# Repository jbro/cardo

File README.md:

# Cardo Keyboard

This is a custom ergonomic wireless keyboard. The design language is based on the [Reviung41](https://github.com/gtips/reviung/tree/master) and the key layout is based on the [Atreus](https://atreus.technomancy.us/) keyboard without thumb keys.

## Features

- Columnar layout
- Low profile
  - Kailh Choc V1 switches
- Sub 40% layout
  - 36 1u keys
  - 1.5u space bar
- Wireless connectivity
- Low part count
  - No diodes
  - Shift register based with a single column
  - Mostly SMD components
- Seeed XIAO nrf52840 micro controller
- 3D printable case (TBD)

## Keymap

## Schematics

## PCB

[3d model](https://github.com/jbro/cardo/blob/main/images/cardo.stl)

## BOM

| Part | Quantity | Description | Link |
| ---- | -------- | ----------- | ---- |
| S2B-PH-SM4-TB(LF)(SN) | 1 | JST PH2 connector | [Mouser](https://www.mouser.dk/ProductDetail/306-S2BPHSM4TBLFSN) |
| SSAJ110100 | 1 | Slide switch | [Mouser](https://www.mouser.dk/ProductDetail/688-SSAJ110100) |
| 7305-0-15-15-47-27-10-0 | 74 | Mill Max 7305 "hot swap" socket | [Mouser](https://www.mouser.dk/ProductDetail/575-7305015154727100) |
| EC05E1220401 | 2 | Rotary encoder | [Mouser](https://www.mouser.dk/ProductDetail/688-EC05E1220401) |
| SN74HCS596DR | 5 | TI shift register with open-drain outputs | [Mouser](https://www.mouser.dk/ProductDetail/Texas-Instruments/SN74HCS596DR) |
| 102010448 | 1 | Seeed XIAO nrf52840 | [Mouser](https://www.mouser.dk/ProductDetail/713-102010448) or  [Seeed studio](https://www.seeedstudio.com/Seeed-XIAO-BLE-nRF52840-p-5201.html) |
| LPR-CHC-SNS-010 | 37 | Kailh Choc Sunset tactile V1 switches | [Splitkb](https://splitkb.com/products/sunset-kailh-low-profile-choc-switches?variant=42742153871619) |
| KSM-MGG-1UN-010 | 34 | 1u MBK PBT Coloured Blank Keycaps | [Splitkb](https://splitkb.com/products/mbk-pbt-coloured-blank-keycaps?variant=49589854011739) |
| KSM-MGG-1UH-002 | 2 | 1u MBK PBT Coloured Blank Keycaps (Homing) | [Splitkb](https://splitkb.com/products/mbk-pbt-coloured-blank-keycaps?variant=49589854404955) |
| KSM-MGG-1U5-002 | 1 | 1.5u MBK PBT Coloured Blank Keycap | [Splitkb](https://splitkb.com/products/mbk-pbt-coloured-blank-keycaps?variant=49589855977819) |
| AM3144y | 1 | Li-Pol battery 60mAh, 3.7V, 501015 | [Ampul](https://ampul.eu/en/battery/4453-li-pol-battery-60mah-37v-501015) |

## License

This project is licensed under the [Unlicense](https://unlicense.org/). Feel free to use, modify, and distribute this project as you wish.

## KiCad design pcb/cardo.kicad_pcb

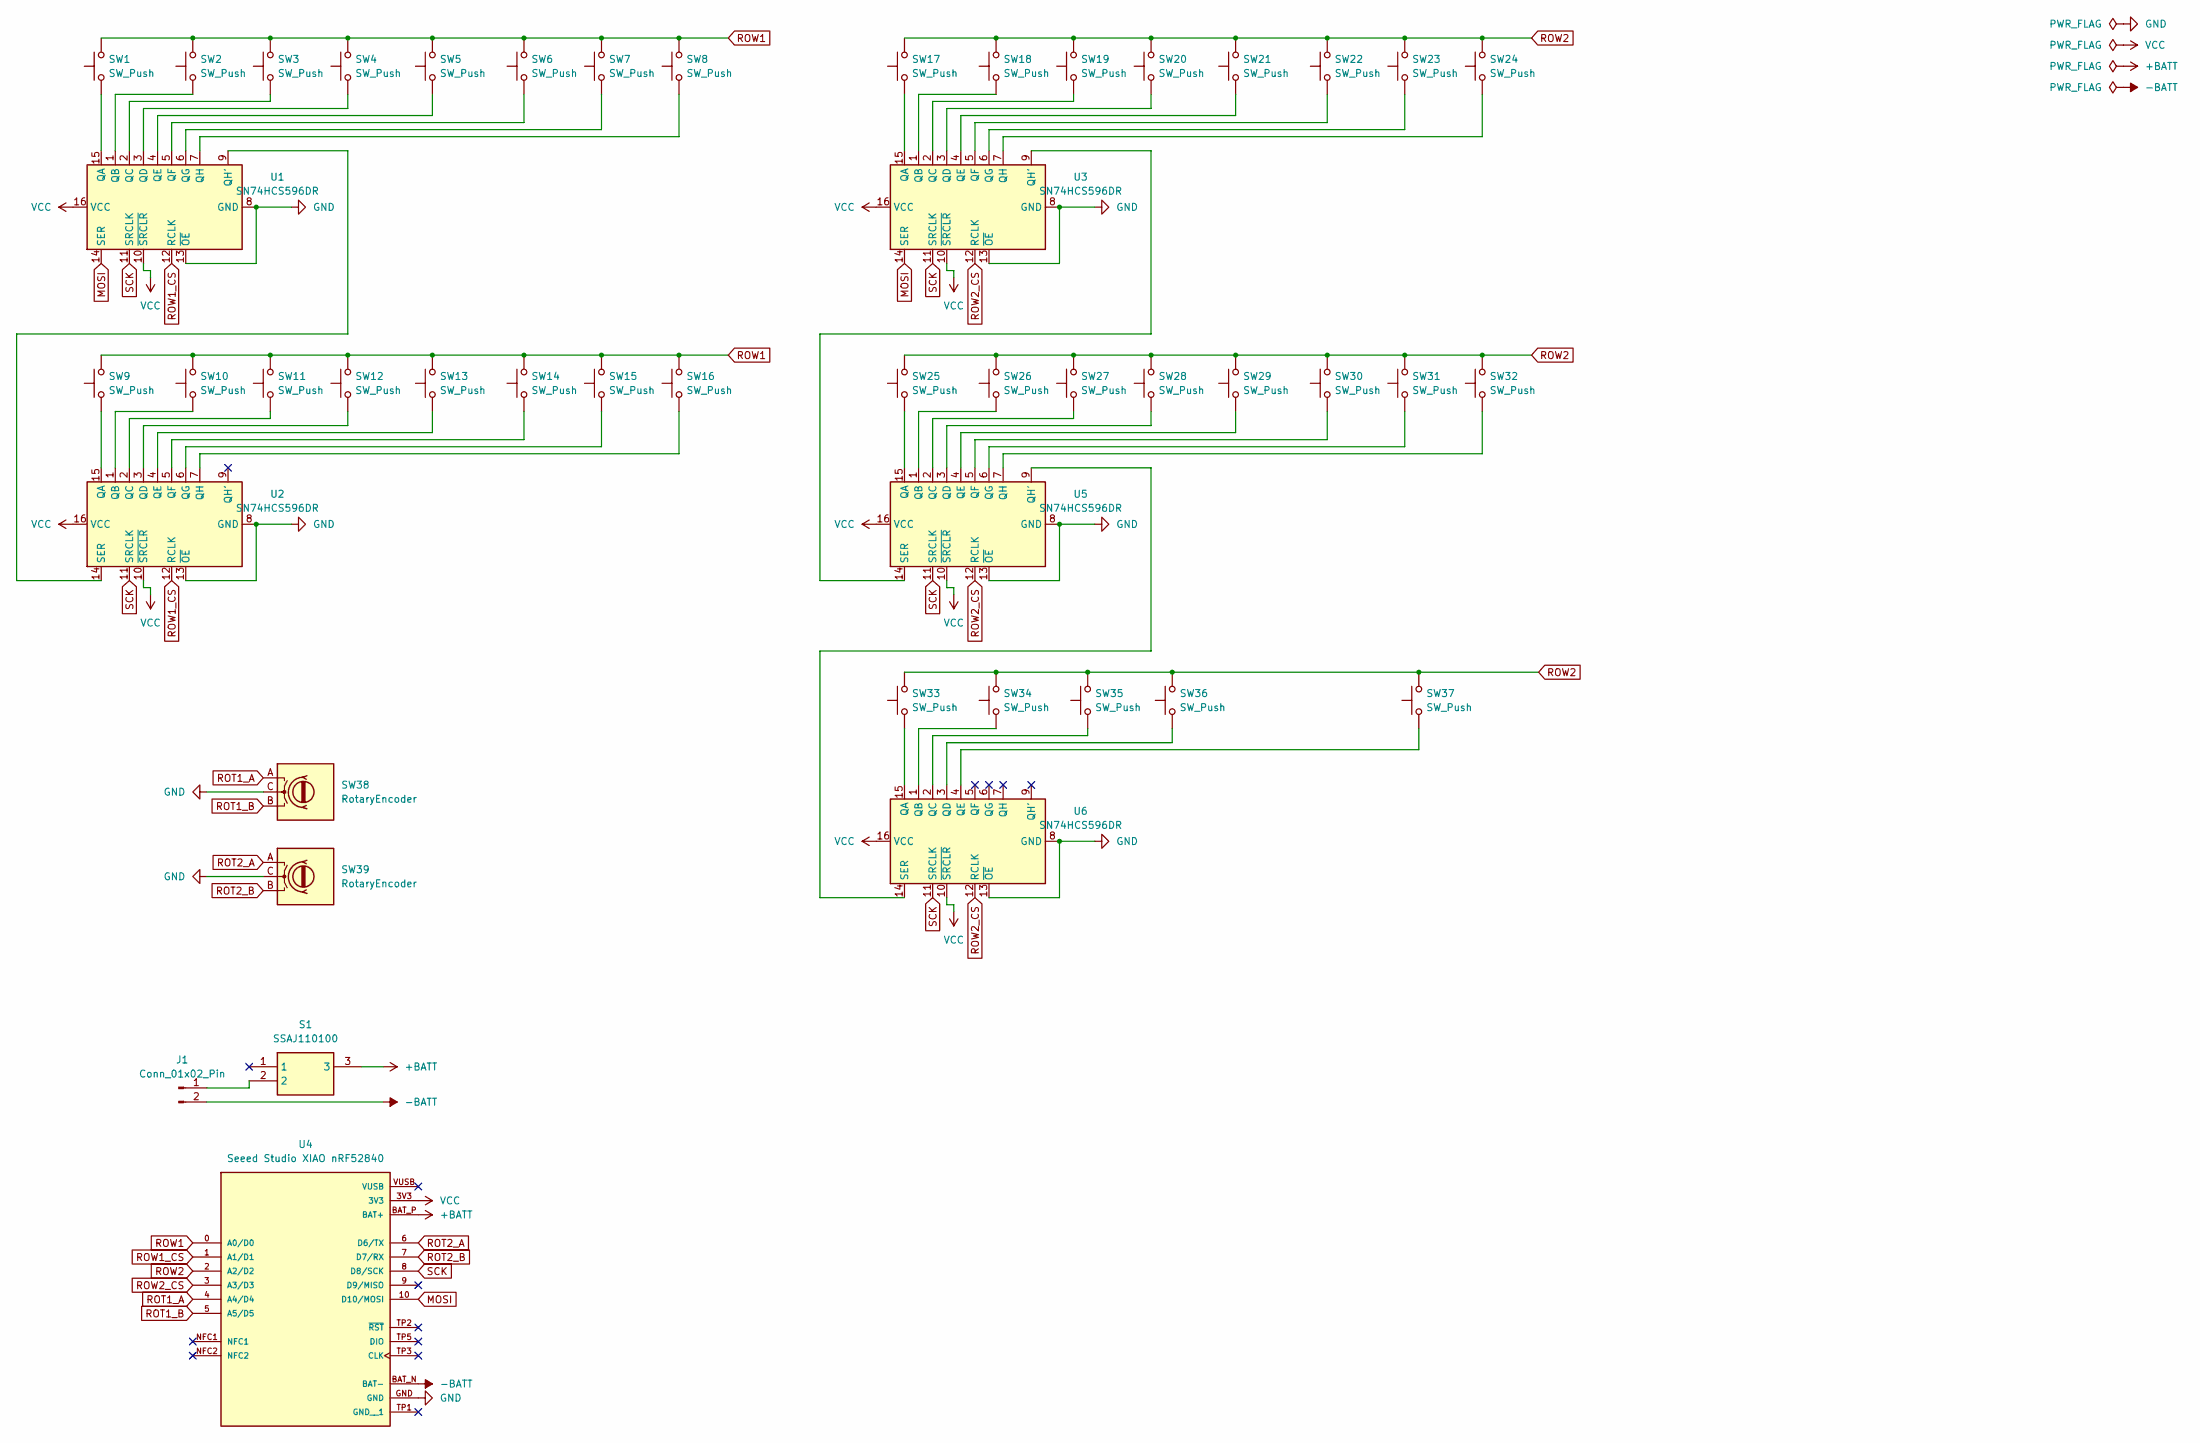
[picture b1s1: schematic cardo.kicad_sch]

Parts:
J1: Conn_01x02_Pin; JST_PH_S2B-PH-SM4-TB_1x02-1MP_P2.00mm_Horizontal
S1: SSAJ110100; SSAJ110100_1; Mouser Part Number 688-SSAJ110100
SW1, SW2, SW3, SW4, SW5, SW6, SW7, SW8, SW9, SW10, SW11, SW12, SW13, SW14, SW15, SW16, SW17, SW18, SW19, SW20, SW21, SW22, SW23, SW24, SW25, SW26, SW27, SW28, SW29, SW30, SW31, SW32, SW33, SW34, SW35, SW36: SW_Push; SW_Kailh_Choc_V1_1.00u
SW37: SW_Push; SW_Kailh_Choc_V1_1.50u
SW38, SW39: RotaryEncoder; Alps EC05E1220401
U1, U2, U3, U5, U6: SN74HCS596DR; SOIC-16_3.9x9.9mm_P1.27mm; Manufacturer_Part_Number SN74HCS596DR
U4: Seeed Studio XIAO nRF52840; PARTREV 2022/08/18

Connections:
+BATT: S1.3, U4.BAT_P (BAT+)
-BATT: J1.2, U4.BAT_N (BAT-)
GND: J1.MP, S1.4, S1.5, SW38.C, SW38.MP, SW39.C, SW39.MP, U1.8 (GND), U1.13 (~OE), U2.8 (GND), U2.13 (~OE), U3.8 (GND), U3.13 (~OE), U4.GND, U5.8 (GND), U5.13 (~OE), U6.8 (GND), U6.13 (~OE)
MOSI: U1.14 (SER), U3.14 (SER), U4.10 (D10/MOSI)
unnamed: J1.1, S1.2
unnamed: SW1.1, U1.15 (QA)
unnamed: SW2.1, U1.1 (QB)
unnamed: SW3.1, U1.2 (QC)
unnamed: SW4.1, U1.3 (QD)
unnamed: SW5.1, U1.4 (QE)
unnamed: SW6.1, U1.5 (QF)
unnamed: SW7.1, U1.6 (QG)
unnamed: U1.9 (QH'), U2.14 (SER)
unnamed: SW8.1, U1.7 (QH)
unnamed: SW9.1, U2.15 (QA)
unnamed: SW10.1, U2.1 (QB)
unnamed: SW11.1, U2.2 (QC)
unnamed: SW12.1, U2.3 (QD)
unnamed: SW13.1, U2.4 (QE)
unnamed: SW14.1, U2.5 (QF)
unnamed: SW15.1, U2.6 (QG)
unnamed: SW16.1, U2.7 (QH)
unnamed: SW17.1, U3.15 (QA)
unnamed: SW18.1, U3.1 (QB)
unnamed: SW19.1, U3.2 (QC)
unnamed: SW20.1, U3.3 (QD)
unnamed: SW21.1, U3.4 (QE)
unnamed: SW22.1, U3.5 (QF)
unnamed: SW23.1, U3.6 (QG)
unnamed: U3.9 (QH'), U5.14 (SER)
unnamed: SW24.1, U3.7 (QH)
unnamed: SW25.1, U5.15 (QA)
unnamed: SW26.1, U5.1 (QB)
unnamed: SW27.1, U5.2 (QC)
unnamed: SW28.1, U5.3 (QD)
unnamed: SW29.1, U5.4 (QE)
unnamed: SW30.1, U5.5 (QF)
unnamed: SW31.1, U5.6 (QG)
unnamed: U5.9 (QH'), U6.14 (SER)
unnamed: SW32.1, U5.7 (QH)
unnamed: SW33.1, U6.15 (QA)
unnamed: SW34.1, U6.1 (QB)
unnamed: SW35.1, U6.2 (QC)
unnamed: SW36.1, U6.3 (QD)
unnamed: SW37.1, U6.4 (QE)
ROT1_A: SW38.A, U4.4 (A4/D4)
ROT1_B: SW38.B, U4.5 (A5/D5)
ROT2_A: SW39.A, U4.6 (D6/TX)
ROT2_B: SW39.B, U4.7 (D7/RX)
ROW1: SW1.2, SW2.2, SW3.2, SW4.2, SW5.2, SW6.2, SW7.2, SW8.2, SW9.2, SW10.2, SW11.2, SW12.2, SW13.2, SW14.2, SW15.2, SW16.2, U4.0 (A0/D0)
ROW1_CS: U1.12 (RCLK), U2.12 (RCLK), U4.1 (A1/D1)
ROW2: SW17.2, SW18.2, SW19.2, SW20.2, SW21.2, SW22.2, SW23.2, SW24.2, SW25.2, SW26.2, SW27.2, SW28.2, SW29.2, SW30.2, SW31.2, SW32.2, SW33.2, SW34.2, SW35.2, SW36.2, SW37.2, U4.2 (A2/D2)
ROW2_CS: U3.12 (RCLK), U4.3 (A3/D3), U5.12 (RCLK), U6.12 (RCLK)
SCK: U1.11 (SRCLK), U2.11 (SRCLK), U3.11 (SRCLK), U4.8 (D8/SCK), U5.11 (SRCLK), U6.11 (SRCLK)
VCC: U1.10 (~SRCLR), U1.16 (VCC), U2.10 (~SRCLR), U2.16 (VCC), U3.10 (~SRCLR), U3.16 (VCC), U4.3V3, U5.10 (~SRCLR), U5.16 (VCC), U6.10 (~SRCLR), U6.16 (VCC)

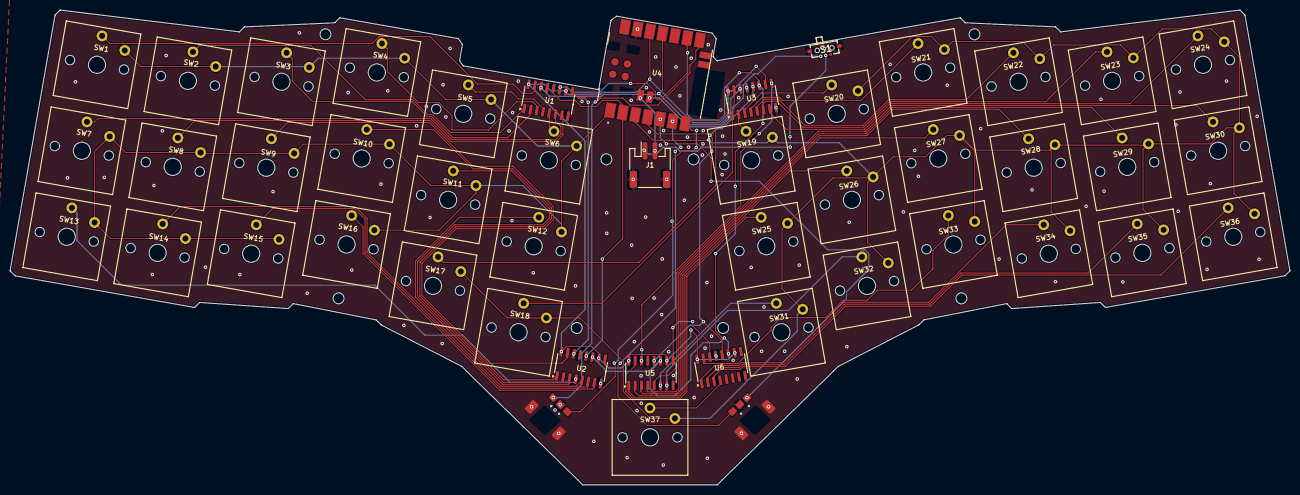
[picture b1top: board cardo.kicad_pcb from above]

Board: 2 copper layers, 256.8 x 95.3 mm, 47 parts (0 on the bottom side), 55 nets.

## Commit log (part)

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2025-06-18 Add BOM
2025-06-18 Update BOM
    - Switches
    - Key caps
    - Battery
2025-06-18 Fix schematic image and update description
